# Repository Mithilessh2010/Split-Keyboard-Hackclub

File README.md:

# Split Keyboard Project

This repository contains the full design for my custom split keyboard, including the PCB, schematic, case files, and bill of materials. Everything needed to build or modify the keyboard is documented here in a clear and approachable format.

## Overview

The keyboard is built around the Seeed XIAO nRF52840 microcontroller, Kailh Choc low profile switches, SOD-123 diodes, and a simple two-piece 3D printed case. The goal of the project is to create a compact split keyboard that is straightforward to assemble and easy to modify.

## Images

All images for the project can be found in the Images folder.

### CAD View (Final, just unmated for clarity)

### PCB Layout

### Schematics

## Bill of Materials

Below is the full set of components used in the keyboard.

### BOM Table

| Category         | Part Description             | Footprint                    | Quantity |
|------------------|------------------------------|------------------------------|----------|
| Resistors        | 806k ohm                     | R_0805_2012Metric            | 2        |
|                  | 2M ohm                       | R_0805_2012Metric            | 2        |
|                  | R (0 ohm or jumper)          | R_0805_2012Metric            | 1        |
| Diodes           | SOD-123 diode                | D_SOD-123                    | 42       |
| Microcontrollers | Seeed XIAO nRF52840          | modified-XIAO-nRF52840-SMD   | 2        |
| Switches         | Kailh Choc V1 switches       | SW_choc_v1_1u                | 41       |
| Test Points      | Test pad                     | TestPoint_Pad_D2.0mm         | 4        |

## 3D Printed Parts

The keyboard uses two printed case parts.

- Top case  
- Bottom case  

Both parts are sized so the PCB fits properly without forcing anything into place.

## Assembly Instructions

1. Install and solder all diodes first. These sit flat on the PCB.
2. Solder all resistors.
3. Insert and solder all Kailh Choc switches.
4. Attach both XIAO nRF52840 modules and verify each pin is properly soldered.
5. Inspect the board and test the key matrix.
6. Place the PCB into the printed case and complete the assembly.

## Cost Breakdown

### AliExpress Order

| Item                                                                 | Quantity | Price    |
|----------------------------------------------------------------------|----------|----------|
| SMD Capacitor and Resistor Book (0603 0805 1206)                    | 1        | $15.33   |
| Kailh Choc V1 Switches (Olive, 90 pcs)                               | 1        | $39.81   |
| RGeek 6.0 W/mK Thermal Pad (200mm x 400mm, 2mm thick)                | 1        | $23.29   |
| Seeed Studio XIAO BLE nRF52840 Module                                | 1        | $22.85   |
| Shipping for XIAO module                                            | 1        | $5.04    |
| Additional charges (import, fees)                                   | —        | $10.38   |
|                                                                      |          |          |
| Subtotal                                                             |          | $101.28  |
| Shipping                                                             |          | $5.04    |
| Additional charges                                                   |          | $10.38   |
| **AliExpress total**                                                 |          | **$116.70** |

### JLCPCB Order

| Item                          | Quantity | Price  |
|-------------------------------|----------|--------|
| PCB prototype (5 boards)      | 5        | $28.92 |

## Total Spent

| Source        | Cost     |
|---------------|----------|
| AliExpress    | $116.70  |
| JLCPCB        | $28.92   |
|               |          |
| **Total spent** | **$145.62** |

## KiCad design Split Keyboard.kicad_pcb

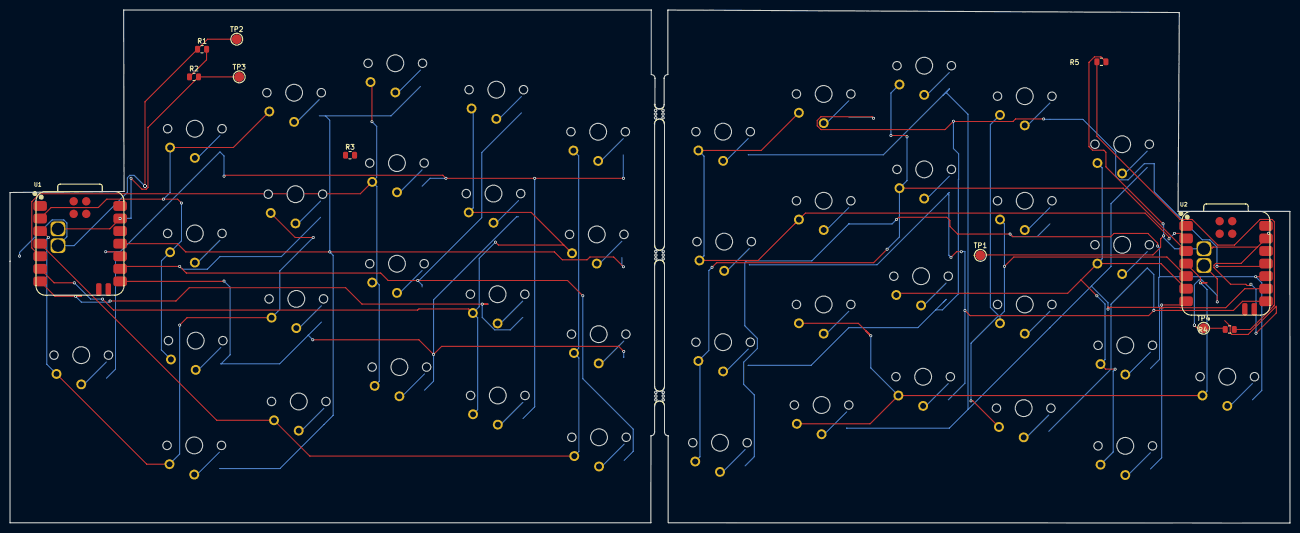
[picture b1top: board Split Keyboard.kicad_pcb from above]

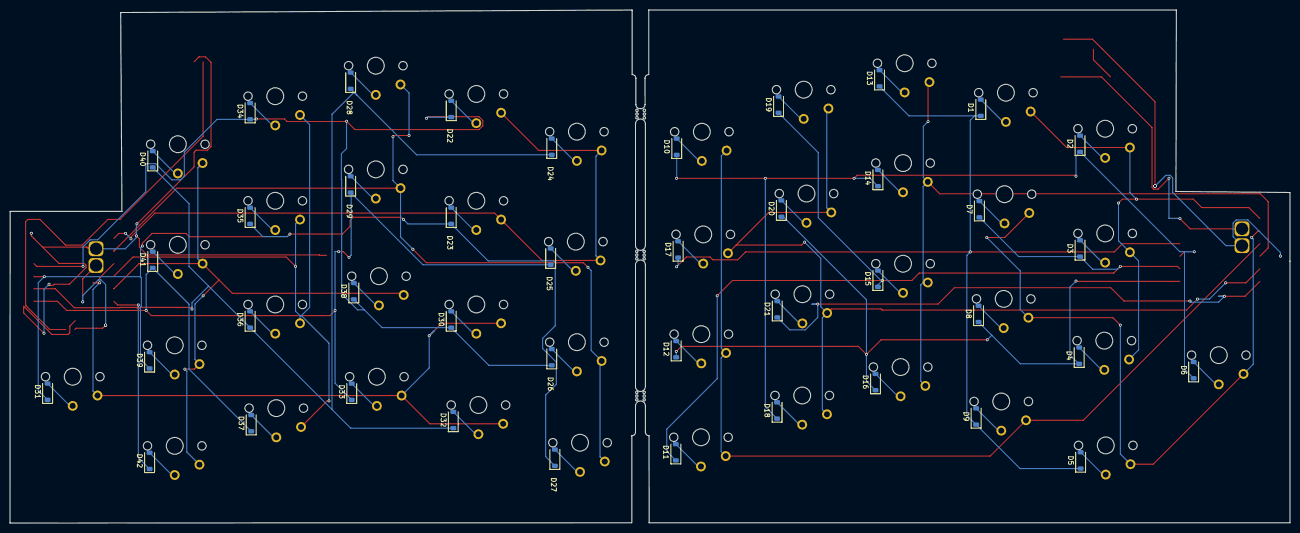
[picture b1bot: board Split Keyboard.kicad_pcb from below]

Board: 2 copper layers, 258.7 x 103.7 mm, 98 parts (42 on the bottom side), 67 nets.

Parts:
BO1, BO2, BO3: break off; mouse-bite-2mm-slot
D1, D2, D3, D4, D5, D6, D7, D8, D9, D10, D11, D12, D13, D14, D15, D16, D17, D18, D19, D20, D21, D22, D23, D24, D25, D26, D27, D28, D29, D30, D31, D32, D33, D34, D35, D36, D37, D38, D39, D40, D41, D42: D; D_SOD-123
R1, R4: 806k; R_0805_2012Metric
R2, R5: 2m; R_0805_2012Metric
R3: R; R_0805_2012Metric
SW1, SW2, SW3, SW4, SW5, SW6, SW7, SW8, SW9, SW10, SW11, SW12, SW13, SW14, SW15, SW16, SW17, SW18, SW19, SW20, SW21, SW22, SW23, SW24, SW25, SW26, SW27, SW28, SW29, SW30, SW31, SW32, SW33, SW34, SW35, SW36, SW37, SW38, SW39, SW40, SW41, SW42: SW_Push; SW_choc_v1_1u
TP1, TP2, TP3, TP4: TestPoint; TestPoint_Pad_D2.0mm
U1, U2: XIAO-nRF52840-SMD; modified-XIAO-nRF52840-SMD

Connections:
/left/BT-PIN: R1.2, R2.1
/left/C0: SW1.1, SW2.1, SW3.1, SW4.1, U1.2 (P0.03_A1_D1)
/left/C1: SW5.1, SW6.1, SW7.1, SW8.1, U1.3 (P0.28_A2_D2)
/left/C2: SW9.1, SW10.1, SW11.1, SW12.1, U1.4 (P0.29_A3_D3)
/left/C3: SW13.1, SW14.1, SW15.1, SW16.1, U1.5 (P0.04_A4_D4_SDA)
/left/C4: SW17.1, SW18.1, SW19.1, SW20.1, SW21.1, U1.6 (P0.05_A5_D5_SCL)
/left/R0: D1.1 (K), D5.1 (K), D9.1 (K), D13.1 (K), D17.1 (K), U1.11 (P1.15_D10_MOSI)
/left/R1: D2.1 (K), D6.1 (K), D10.1 (K), D14.1 (K), D18.1 (K), U1.10 (P1.14_D9_MISO)
/left/R4: D21.1 (K), U1.7 (P1.11_D6_TX)
/left/Ro2: D3.1 (K), D7.1 (K), D11.1 (K), D15.1 (K), D19.1 (K), U1.9 (P1.13_D8_SCK)
/left/Ro3: D4.1 (K), D8.1 (K), D12.1 (K), D16.1 (K), D20.1 (K), U1.8 (P1.12_D7_RX)
/left/VBAT: R1.1, TP2.1, U1.15 (BAT)
/right/BT-PIN: R4.2, R5.1
/right/C0: SW22.1, SW23.1, SW24.1, SW25.1, U2.2 (P0.03_A1_D1)
/right/C1: SW26.1, SW27.1, SW28.1, SW29.1, U2.3 (P0.28_A2_D2)
/right/C2: SW30.1, SW31.1, SW32.1, SW33.1, U2.4 (P0.29_A3_D3)
/right/C3: SW34.1, SW35.1, SW36.1, SW37.1, U2.5 (P0.04_A4_D4_SDA)
/right/C4: SW38.1, SW39.1, SW40.1, SW41.1, SW42.1, U2.6 (P0.05_A5_D5_SCL)
/right/R0: D22.1 (K), D26.1 (K), D30.1 (K), D34.1 (K), D38.1 (K), U2.11 (P1.15_D10_MOSI)
/right/R1: D23.1 (K), D27.1 (K), D31.1 (K), D35.1 (K), D39.1 (K), U2.10 (P1.14_D9_MISO)
/right/R4: D42.1 (K), U2.7 (P1.11_D6_TX)
/right/Ro2: D24.1 (K), D28.1 (K), D32.1 (K), D36.1 (K), D40.1 (K), U2.9 (P1.13_D8_SCK)
/right/Ro3: D25.1 (K), D29.1 (K), D33.1 (K), D37.1 (K), D41.1 (K), U2.8 (P1.12_D7_RX)
/right/VBAT: R4.1, TP4.1, U2.15 (BAT)
GND: R2.2, R5.2, TP1.1, TP3.1, U1.13 (GND), U1.16 (GND), U2.13 (GND), U2.16 (GND)
unnamed: D1.2 (A), SW1.2
unnamed: D2.2 (A), SW2.2
unnamed: D3.2 (A), SW3.2
unnamed: D4.2 (A), SW4.2
unnamed: D5.2 (A), SW5.2
unnamed: D6.2 (A), SW6.2
unnamed: D7.2 (A), SW7.2
unnamed: D8.2 (A), SW8.2
unnamed: D9.2 (A), SW9.2
unnamed: D10.2 (A), SW10.2
unnamed: D11.2 (A), SW11.2
unnamed: D12.2 (A), SW12.2
unnamed: D13.2 (A), SW13.2
unnamed: D14.2 (A), SW14.2
unnamed: D15.2 (A), SW15.2
unnamed: D16.2 (A), SW16.2
unnamed: D17.2 (A), SW17.2
unnamed: D18.2 (A), SW18.2
unnamed: D19.2 (A), SW19.2
unnamed: D20.2 (A), SW20.2
unnamed: D21.2 (A), SW21.2
unnamed: D22.2 (A), SW22.2
unnamed: D23.2 (A), SW23.2
unnamed: D24.2 (A), SW24.2
unnamed: D25.2 (A), SW25.2
unnamed: D26.2 (A), SW26.2
unnamed: D27.2 (A), SW27.2
unnamed: D28.2 (A), SW28.2
unnamed: D29.2 (A), SW29.2
unnamed: D30.2 (A), SW30.2
unnamed: D31.2 (A), SW31.2
unnamed: D32.2 (A), SW32.2
unnamed: D33.2 (A), SW33.2
unnamed: D34.2 (A), SW34.2
unnamed: D35.2 (A), SW35.2
unnamed: D36.2 (A), SW36.2
unnamed: D37.2 (A), SW37.2
unnamed: D38.2 (A), SW38.2
unnamed: D39.2 (A), SW39.2
unnamed: D40.2 (A), SW40.2
unnamed: D41.2 (A), SW41.2
unnamed: D42.2 (A), SW42.2

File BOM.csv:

"Id";"Designator";"Footprint";"Quantity";"Designation";"Supplier and ref";
1;"SW37,SW4,SW15,SW17,SW1,SW30,SW6,SW5,SW7,SW29,SW26,SW20,SW22,SW35,SW2,SW24,SW21,SW39,SW28,SW31,SW23,SW12,SW36,SW32,SW41,SW27,SW3,SW9,SW42,SW16,SW38,SW19,SW33,SW14,SW18,SW8,SW40,SW25,SW11,SW13,SW34";"SW_choc_v1_1u";41;"SW_Push";;;
2;"D9,D19,D40,D37,D28,D1,D42,D12,D16,D8,D18,D24,D25,D3,D15,D17,D2,D31,D5,D13,D10,D38,D21,D36,D34,D23,D11,D35,D41,D39,D14,D32,D33,D30,D29,D26,D27,D22,D20,D7,D6,D4";"D_SOD-123";42;"D";;;
3;"TP2,TP4,TP1,TP3";"TestPoint_Pad_D2.0mm";4;"TestPoint";;;
4;"U2,U1";"modified-XIAO-nRF52840-SMD";2;"XIAO-nRF52840-SMD";;;
5;"R5,R2";"R_0805_2012Metric";2;"2m";;;
6;"R4,R1";"R_0805_2012Metric";2;"806k";;;
7;"R3";"R_0805_2012Metric";1;"R";;;

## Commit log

2025-12-03 Initialize keyboard firmware with keymap and matrix
2025-12-05 Change CAD image to direct URL link
    Updated CAD image link to use a direct URL.
2025-12-05 Revise README for clarity and formatting
    Updated the README for clarity and consistency in language, improved formatting for BOM and assembly instructions.
2025-12-05 Update CAD View description and JLCPCB image
2025-12-05 Add CAD images with links to README
    Added additional CAD images with links to GitHub.
2025-12-06 Rename tops.step to case.step
